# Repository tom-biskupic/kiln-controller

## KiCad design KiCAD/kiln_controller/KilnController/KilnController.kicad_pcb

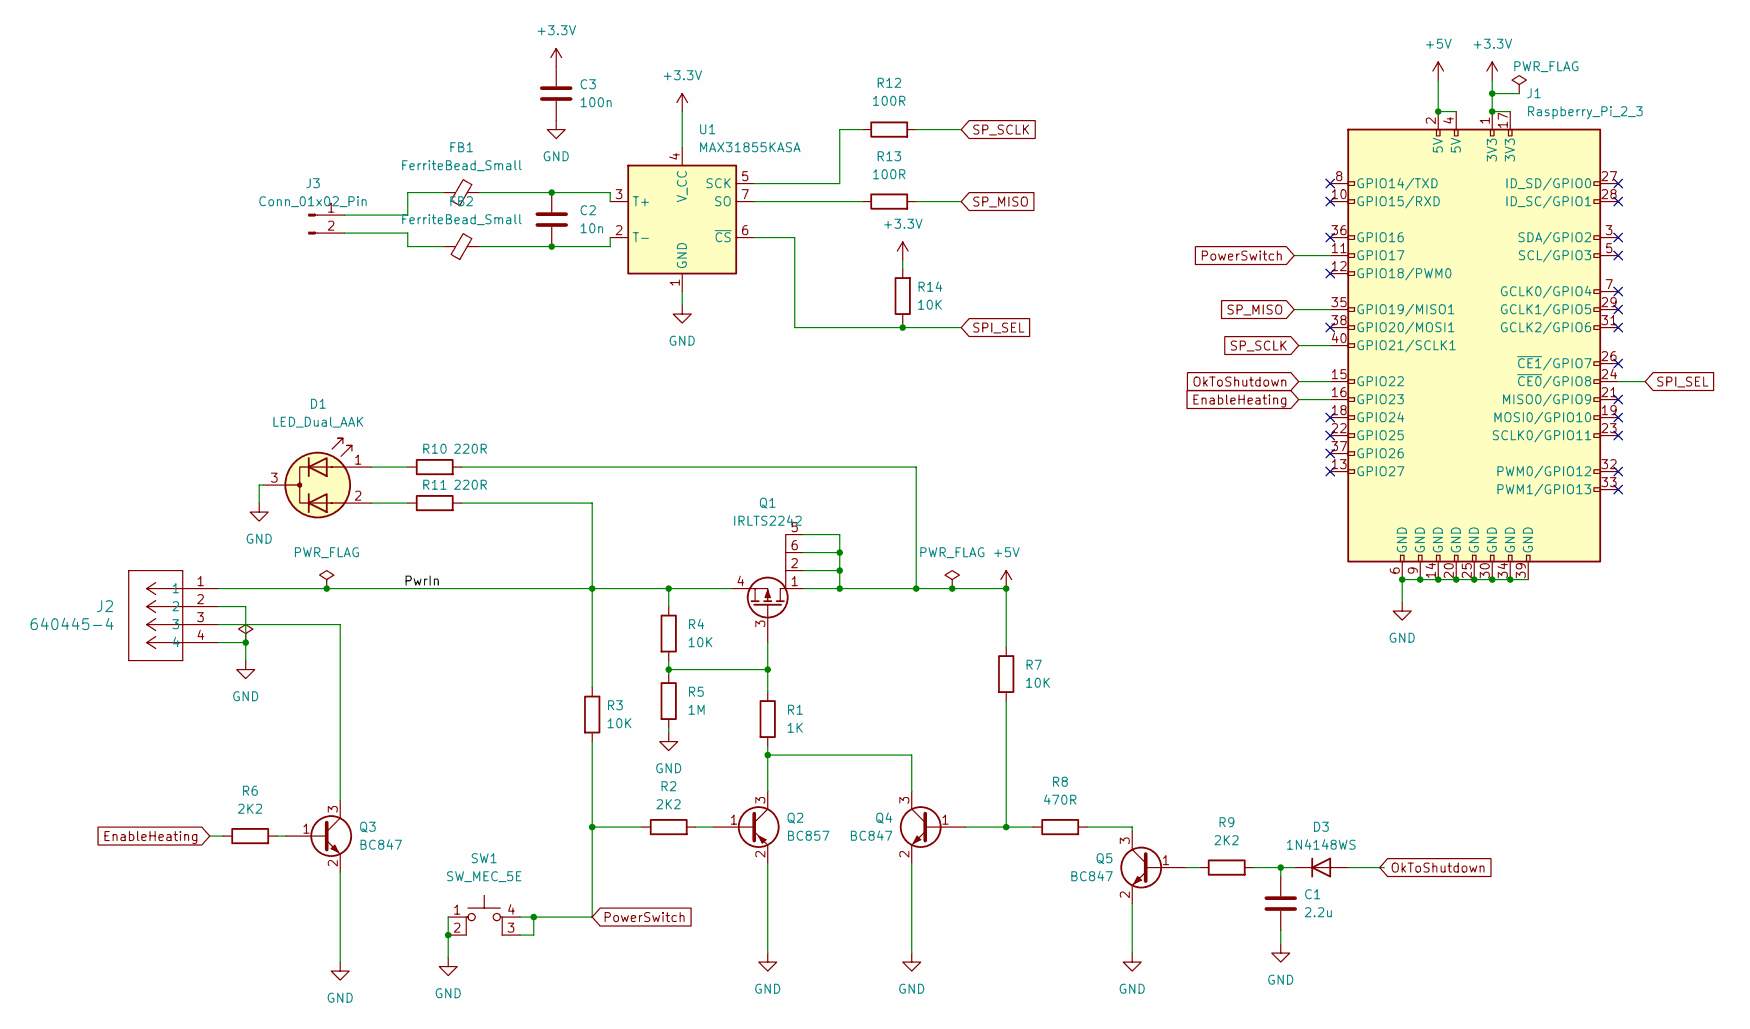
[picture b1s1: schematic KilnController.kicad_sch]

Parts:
C1: 2.2u; C_0805_2012Metric
C2: 10n; C_0805_2012Metric
C3: 100n; C_0805_2012Metric
D1: LED_Dual_AAK; LED_D5.0mm-3
D3: 1N4148WS; D_SOD-323
FB1, FB2: FerriteBead_Small; R_0805_2012Metric_Pad1.20x1.40mm_HandSolder
J1: Raspberry_Pi_2_3; PinHeader_2x20_P2.54mm_Vertical
J2: 640445-4; CONN4_640445-4_TEC
J3: Conn_01x02_Pin; 1x2ScrewTerminal
Q1: IRLTS2242; TSOP-6_1.65x3.05mm_P0.95mm
Q2: BC857; SOT-23
Q3, Q4, Q5: BC847; SOT-23
R1: 1K; R_0805_2012Metric_Pad1.20x1.40mm_HandSolder
R2, R6, R9: 2K2; R_0805_2012Metric_Pad1.20x1.40mm_HandSolder
R3, R4, R7, R14: 10K; R_0805_2012Metric_Pad1.20x1.40mm_HandSolder
R5: 1M; R_0805_2012Metric_Pad1.20x1.40mm_HandSolder
R8: 470R; R_0805_2012Metric_Pad1.20x1.40mm_HandSolder
R10, R11: 220R; R_0805_2012Metric_Pad1.20x1.40mm_HandSolder
R12, R13: 100R; R_0805_2012Metric_Pad1.20x1.40mm_HandSolder
SW1: SW_MEC_5E; Push_E-Switch_KS01Q01
U1: MAX31855KASA; SOIC-8_3.9x4.9mm_P1.27mm

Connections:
+3.3V: C3.1, J1.1 (3V3), J1.17 (3V3), R14.2, U1.4 (V_CC)
+5V: J1.2 (5V), J1.4 (5V), Q1.1 (D), Q1.2 (D), Q1.5 (D), Q1.6 (D), R7.1, R10.2
/PwrIn: J2.1, Q1.4 (S), R3.1, R4.1, R11.2
EnableHeating: J1.16 (GPIO23), R6.1
GND: C1.2, C3.2, D1.3 (K), J1.6 (GND), J1.9 (GND), J1.14 (GND), J1.20 (GND), J1.25 (GND), J1.30 (GND), J1.34 (GND), J1.39 (GND), J2.2, J2.4, Q2.2 (E), Q3.2 (E), Q4.2 (E), Q5.2 (E), R5.2, SW1.1, SW1.2, U1.1 (GND)
unnamed: D1.1 (A1), R10.1
unnamed: D1.2 (A2), R11.1
unnamed: C1.1, D3.1 (K), R9.2
unnamed: FB1.1, J3.1
unnamed: FB2.1, J3.2
unnamed: Q1.3 (G), R1.1, R4.2, R5.1
unnamed: Q2.1 (B), R2.2
unnamed: Q2.3 (C), Q4.3 (C), R1.2
unnamed: Q3.1 (B), R6.2
unnamed: J2.3, Q3.3 (C)
unnamed: Q4.1 (B), R7.2, R8.1
unnamed: Q5.1 (B), R9.1
unnamed: Q5.3 (C), R8.2
unnamed: R12.1, U1.5 (SCK)
unnamed: R13.1, U1.7 (SO)
unnamed: C2.1, FB1.2, U1.3 (T+)
unnamed: C2.2, FB2.2, U1.2 (T-)
OkToShutdown: D3.2 (A), J1.15 (GPIO22)
PowerSwitch: J1.11 (GPIO17), R2.1, R3.2, SW1.3 (K), SW1.4 (A)
SPI_SEL: J1.24 (~CE0/GPIO8), R14.1, U1.6 (~CS)
SP_MISO: J1.35 (GPIO19/MISO1), R13.2
SP_SCLK: J1.40 (GPIO21/SCLK1), R12.2

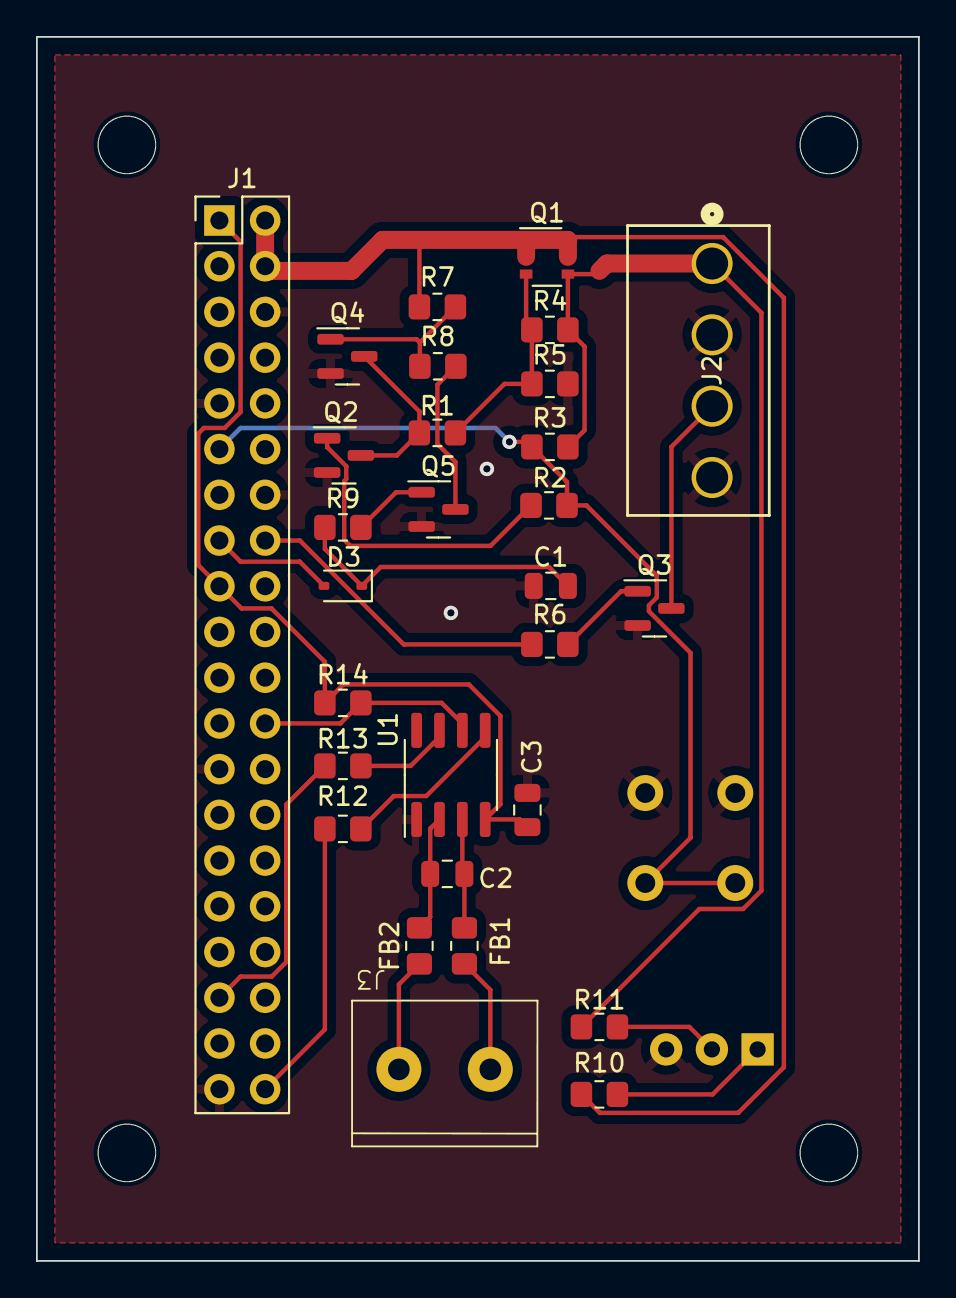
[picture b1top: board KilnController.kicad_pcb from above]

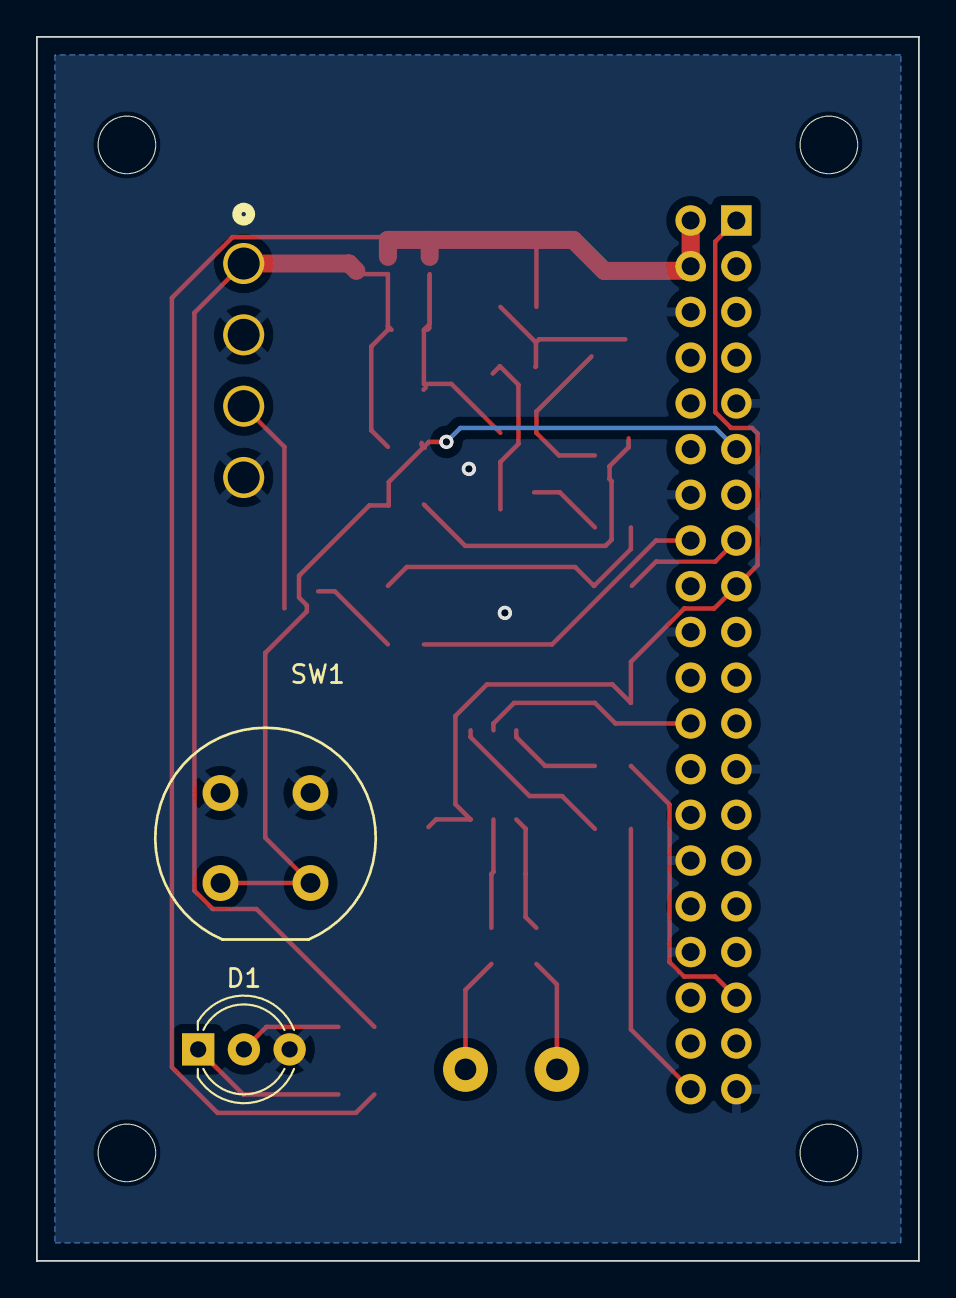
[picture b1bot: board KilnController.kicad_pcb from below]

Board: 2 copper layers, 49.0 x 68.0 mm, 31 parts (2 on the bottom side), 27 nets.

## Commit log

2024-11-22 Initial version of Kiln controller power control board
